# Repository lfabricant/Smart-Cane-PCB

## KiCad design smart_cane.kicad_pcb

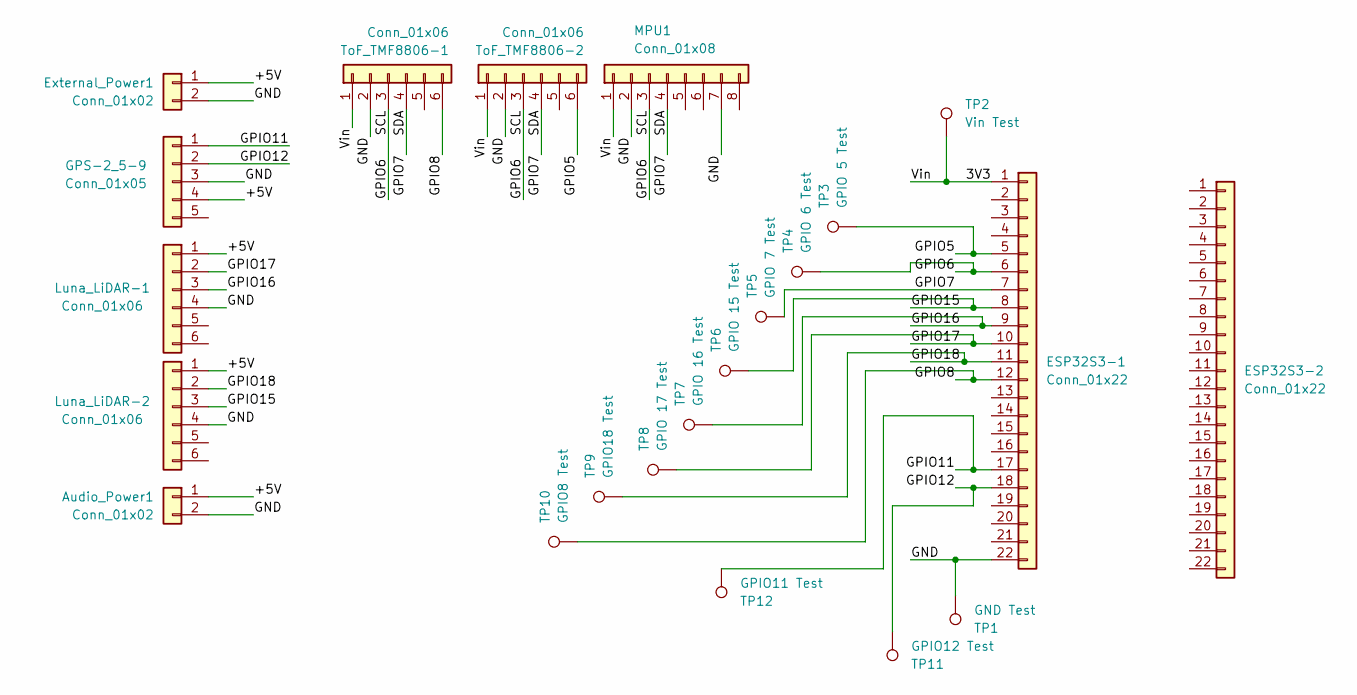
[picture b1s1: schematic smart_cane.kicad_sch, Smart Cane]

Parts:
Audio_Power1: Conn_01x02; TE_640457-2
ESP32S3-1, ESP32S3-2: Conn_01x22; PinSocket_1x22_P2.54mm_Vertical
External_Power1: Conn_01x02; TE_640457-2
GPS-2_5-9: Conn_01x05; TE_640457-5
Luna_LiDAR-1, Luna_LiDAR-2: Conn_01x06; TE_640457-6
MPU1: Conn_01x08; TE_640457-8
TP1: GND Test; TestPoint_Pad_1.0x1.0mm
TP2: Vin Test; TestPoint_Pad_1.0x1.0mm
TP3: GPIO 5 Test; TestPoint_Pad_1.0x1.0mm
TP4: GPIO 6 Test; TestPoint_Pad_1.0x1.0mm
TP5: GPIO 7 Test; TestPoint_Pad_1.0x1.0mm
TP6: GPIO 15 Test; TestPoint_Pad_1.0x1.0mm
TP7: GPIO 16 Test; TestPoint_Pad_1.0x1.0mm
TP8: GPIO 17 Test; TestPoint_Pad_1.0x1.0mm
TP9: GPIO18 Test; TestPoint_Pad_1.0x1.0mm
TP10: GPIO8 Test; TestPoint_Pad_1.0x1.0mm
TP11: GPIO12 Test; TestPoint_Pad_1.0x1.0mm
TP12: GPIO11 Test; TestPoint_Pad_1.0x1.0mm
ToF_TMF8806-1, ToF_TMF8806-2: Conn_01x06; TE_640457-6

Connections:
/3V3: ESP32S3-1.1, MPU1.1, TP2.1 (1_1), ToF_TMF8806-1.1, ToF_TMF8806-2.1
/+5V: Audio_Power1.1, External_Power1.1, GPS-2_5-9.4, Luna_LiDAR-1.1, Luna_LiDAR-2.1
/GND: Audio_Power1.2, ESP32S3-1.22, External_Power1.2, GPS-2_5-9.3, Luna_LiDAR-1.4, Luna_LiDAR-2.4, MPU1.2, MPU1.7, TP1.1 (1_1), ToF_TMF8806-1.2, ToF_TMF8806-2.2
/GPIO5: ESP32S3-1.5, TP3.1 (1_1), ToF_TMF8806-2.6
/GPIO6: ESP32S3-1.6, MPU1.3, TP4.1 (1_1), ToF_TMF8806-1.3, ToF_TMF8806-2.3
/GPIO7: ESP32S3-1.7, MPU1.4, TP5.1 (1_1), ToF_TMF8806-1.4, ToF_TMF8806-2.4
/GPIO8: ESP32S3-1.12, TP10.1 (1_1), ToF_TMF8806-1.6
/GPIO11: ESP32S3-1.17, GPS-2_5-9.1, TP12.1 (1_1)
/GPIO12: ESP32S3-1.18, GPS-2_5-9.2, TP11.1 (1_1)
/GPIO15: ESP32S3-1.8, Luna_LiDAR-2.3, TP6.1 (1_1)
/GPIO16: ESP32S3-1.9, Luna_LiDAR-1.3, TP7.1 (1_1)
/GPIO17: ESP32S3-1.10, Luna_LiDAR-1.2, TP8.1 (1_1)
/GPIO18: ESP32S3-1.11, Luna_LiDAR-2.2, TP9.1 (1_1)

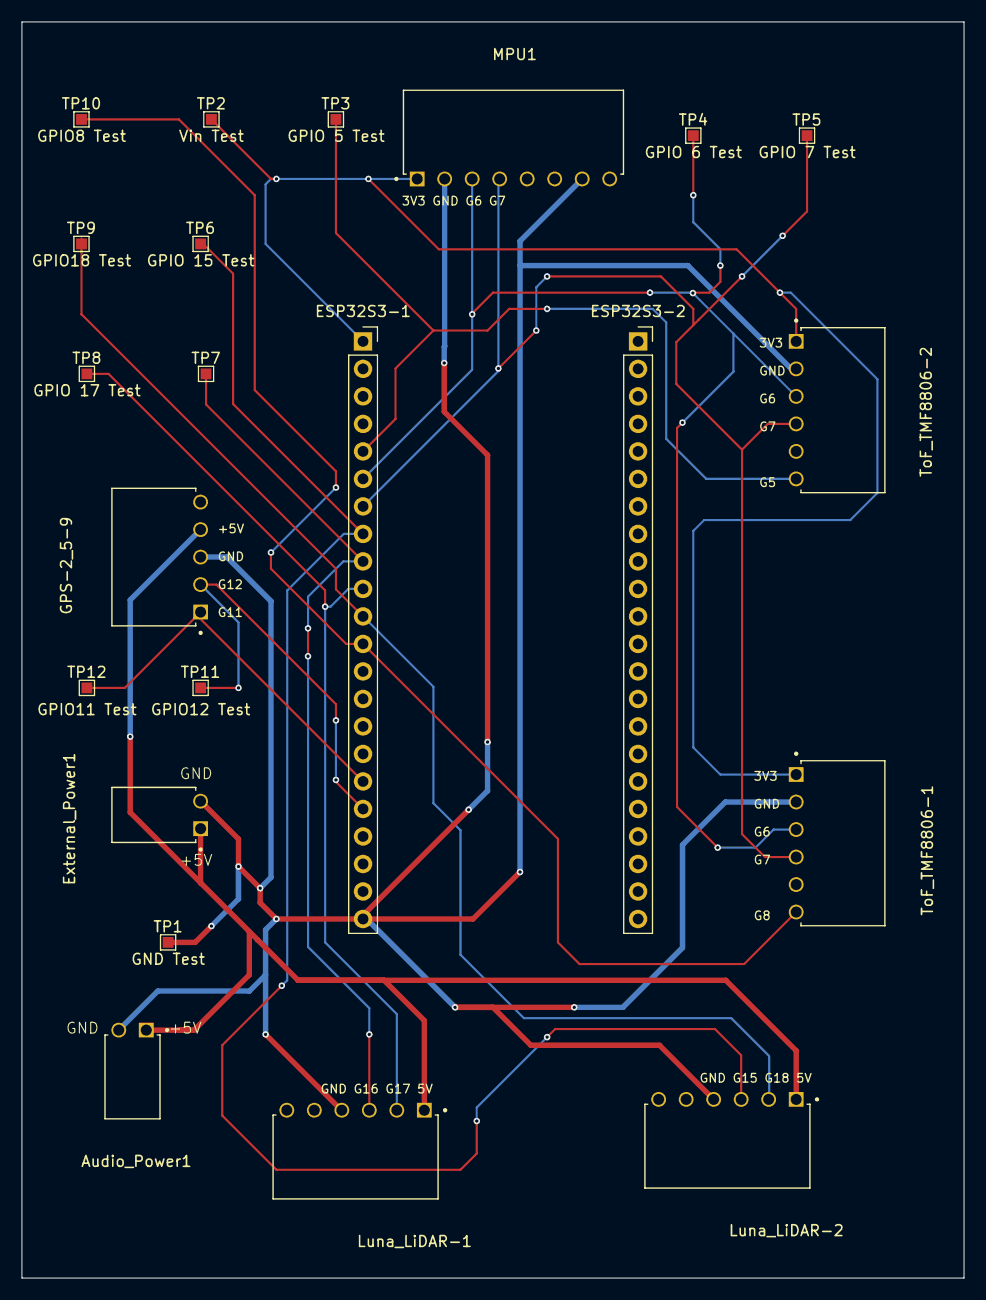
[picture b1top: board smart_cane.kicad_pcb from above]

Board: 2 copper layers, 87.0 x 116.0 mm, 22 parts (0 on the bottom side), 13 nets.
